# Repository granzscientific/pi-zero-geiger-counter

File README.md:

# pyGI/webGI - A Web interface for the Granz Scientific Raspberry Pi Zero Geiger Counter

Python/HTML5/CSS/JS/Websocket software suite for collecting, distributing,
monitoring, mapping and analyzing ionizing radiation counts detected by the PiGI-Module.

This software stack is based on the Raspberry Pi Geiger Counter project described here:

http://projects-raspberry.com/pigi-raspberry-pi-geiger-muller-interface/

and here:

https://apollo.open-resource.org/lab:pigi

## Sneak-Preview: Development screenshots in action

### Main instrument panel

### History instrument panel

### Ion trace visualizer

## Installation

### Dependencies

We've tried to keep external dependencies to a minimum to make it easily
deployable on any flavor of open-source operating system. If you deploy it
successfully on any other OS, please update this:

#### Currently tested versions

    * greenlet-0.4.2
    * bottle-0.12.4
    * gevent-1.0
    * gevent-websocket-0.9.3

#### Ubuntu/Raspbian

    $ sudo apt-get install python-pip python-dev libevent-dev
    $ sudo pip install ez-setup
    $ sudo pip install leveldb greenlet bottle gevent gevent-websocket

#### Raspberry Pi deployment

If you want to deploy the code on a Pi for production in order to count
values from a real GM tube connected to the Pi, you have to make sure to
satisfy the RPi.GPIO dependency:

    * pip install RPi.GPIO

This only applies to non-Raspbian installations, since Raspbian ships
RPi.GPIO with the default installation.

### Clone repo

    $ git clone https://github.com/granzscientific/pi-zero-geiger-counter.git

## Configuration

PyGI checks 3 configuration files, if existent in conf/, updating the
values defined in the file before or using new ones, in the following order:

    * default.cfg (automatically comes shipped per default with examples)
    * local.cfg (create this file to override local server settings - gitignored)
    * dynamic.cfg (this file will be created automatically,
      if the webGI client wants to change server settings - also gitignored)

When you are deploying on the Pi to count real values and/or want to
change the Web Server/Socket port to 80 rather than 8080 __you have to
run the software as root__. Otherwise the interrupt handling on the Pi
won't work and port 80 will not be accessible due to security (<1024).

## Usage

### Server Startup

    $ cd PiGI/
    $ ./pyGIserver.py

### Client Access

Open Browser and goto http://localhost:8080

### License

This program is free software: you can redistribute it and/or modify
it under the terms of the GNU General Public License as published by
the Free Software Foundation, either version 3 of the License, or
(at your option) any later version.

This program is distributed in the hope that it will be useful,
but WITHOUT ANY WARRANTY; without even the implied warranty of
MERCHANTABILITY or FITNESS FOR A PARTICULAR PURPOSE.  See the
GNU General Public License for more details.

You should have received a copy of the GNU General Public License
along with this program.  If not, see <http://www.gnu.org/licenses/>.

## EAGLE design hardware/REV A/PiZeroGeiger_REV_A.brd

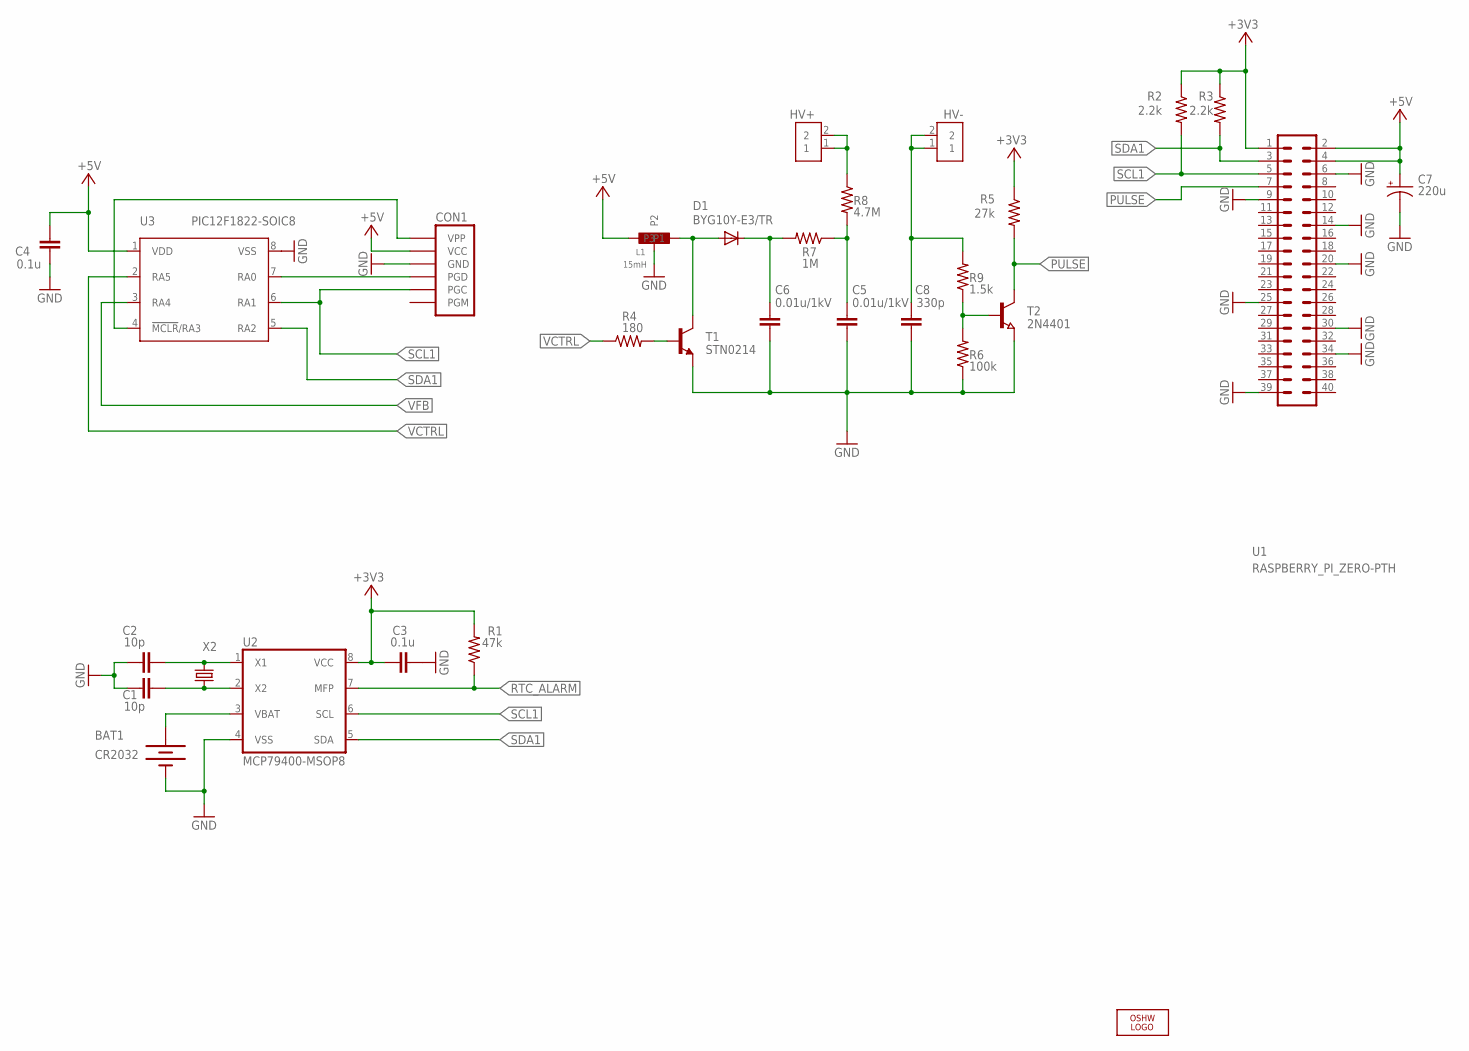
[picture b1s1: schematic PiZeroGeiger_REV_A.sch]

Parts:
BAT1: CR2032; BATTERY_HOLDER_12MM_BK-885
C1, C2: 10p; RCL_0805
C3, C4: 0.1u; RCL_0805
C5, C6: 0.01u/1kV; RCL_1812
C7: 220u; CAPACITOR_POLARIZED_PTH_2.5MM-7MM
C8: 330p; RCL_0805
CON1: CON_PIC_ICSP; CON_INLINE_TE_640456-6
D1: BYG10Y-E3/TR; DO-214AC
HV+: FUSE_HOLDER-PTH; FUSE_HOLDER_PTH
HV-: FUSE_HOLDER-PTH; FUSE_HOLDER_PTH
L1: 15mH; 1200LRS
LOGO1: OSHW_LOGO_FILLX0150-NT; OSHW_FILLX150_NOTEXT
R1: 47k; RCL_0805
R2, R3: 2.2k; RCL_0805
R4: 180; RCL_0805
R5: 27k; RCL_0805
R6: 100k; RCL_0805
R7: 1M; RCL_0805
R8: 4.7M; RCL_0805
R9: 1.5k; RCL_0805
T1: STN0214; SOT223
T2: 2N4401; SOT23
U1: RASPBERRY_PI_ZERO-PTH; RASPBERRY_PI_ZERO
U2: MCP79400-MSOP8; MSOP8
U3: PIC12F1822-SOIC8; SOIC8
X2: 32.768 kHz 12.5 pF X1123-ND; CRYSTAL_ABRACON_ABS10

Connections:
+3V3: C3.2, R1.2, R2.1, R3.1, R5.1, U1.1, U2.8 (VCC)
+5V: C4.1, C7.+, CON1.5 (VCC), L1.P1, U1.2, U1.4, U3.1 (VDD)
DIS: R4.2, T1.1 (B)
GND: BAT1.-, C1.2, C2.2, C3.1, C4.2, C5.2, C6.2, C7.-, C8.2, CON1.4 (GND), L1.P4 (P2), R6.1, T1.3 (E), T2.2 (E), U1.6, U1.9, U1.14, U1.20, U1.25, U1.30, U1.34, U1.39, U2.4 (VSS), U3.8 (VSS)
unnamed: CON1.6 (VPP), U3.4 (!MCLR!/RA3)
unnamed: C6.1, D1.C, R7.2
unnamed: CON1.3 (PGD), U3.7 (RA0)
unnamed: D1.A, L1.P3, T1.4 (C)
unnamed: C5.1, R7.1, R8.2
unnamed: R6.2, R9.1, T2.1 (B)
unnamed: C8.1, HV-.1, HV-.2, R9.2
unnamed: HV+.1, HV+.2, R8.1
unnamed: C1.1, U2.2 (X2), X2.1
unnamed: C2.1, U2.1 (X1), X2.2
unnamed: BAT1.+A (+), U2.3 (VBAT)
PULSE: R5.2, T2.3 (C), U1.7
RTC_ALARM: R1.1, U2.7 (MFP)
SCL1: CON1.2 (PGC), R2.2, U1.5, U2.6 (SCL), U3.6 (RA1)
SDA1: R3.2, U1.3, U2.5 (SDA), U3.5 (RA2)
VCTRL: R4.1, U3.2 (RA5)
VFB: U3.3 (RA4)

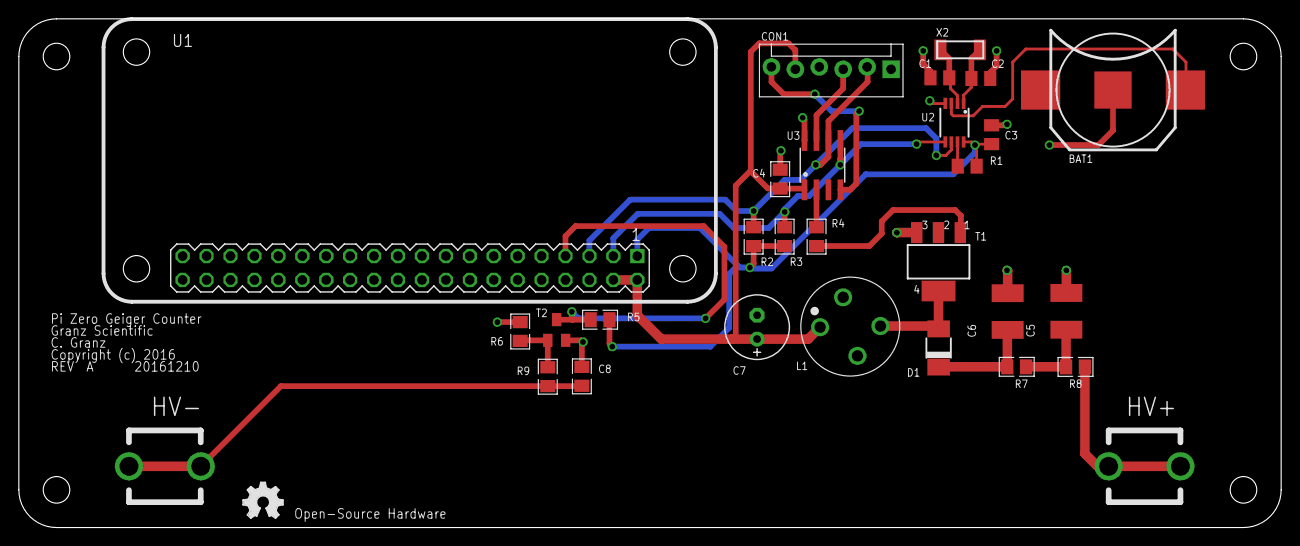
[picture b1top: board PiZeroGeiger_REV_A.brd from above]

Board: 2 copper layers, 134.0 x 54.0 mm, 31 parts (0 on the bottom side), 20 nets.

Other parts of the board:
U$1: INFO_BOARD1

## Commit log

2017-03-22 Initial commit.
2017-03-22 Fixed README.
2017-03-22 More README fixes.
2017-04-13 Added hardware design files and PIC firmware.
2017-04-24 Fixed disconnect issue with web interface (hopefully). Fixed README to correct Pi Zero version (not old apollo version). Other minor changes.
2017-04-24 Re-enabled HV supply in pyGI server.
2017-04-24 Fixed default input pin in pyGI server.
2017-04-24 Slight changed to pulse width for HV tube supply. Added geiger_off.py to quickly turn off the HV supply.
2017-04-24 Fixed the README.
2017-05-04 Whitespace. Python3 compatibility fixes (imports still need to be fixed). Some errors fixed.
2017-07-03 Added pyGIconsole.py.
2017-07-03 Fix to turn off HV supply when program exits. Renamed geiger_off.py and geiger_test.py to geigeroff.py and geigertest.py for consistency. Added pyGIconsole.py which runs the same geigercounter module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
2017-07-03 Fixed formatting.
2017-07-03 Fixed MPLAB-X Project dir name for PIC firmware.

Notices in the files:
hardware/REV A/PiZeroGeiger_REV_A.brd:
COPYRIGHT: Copyright (c) 2016
